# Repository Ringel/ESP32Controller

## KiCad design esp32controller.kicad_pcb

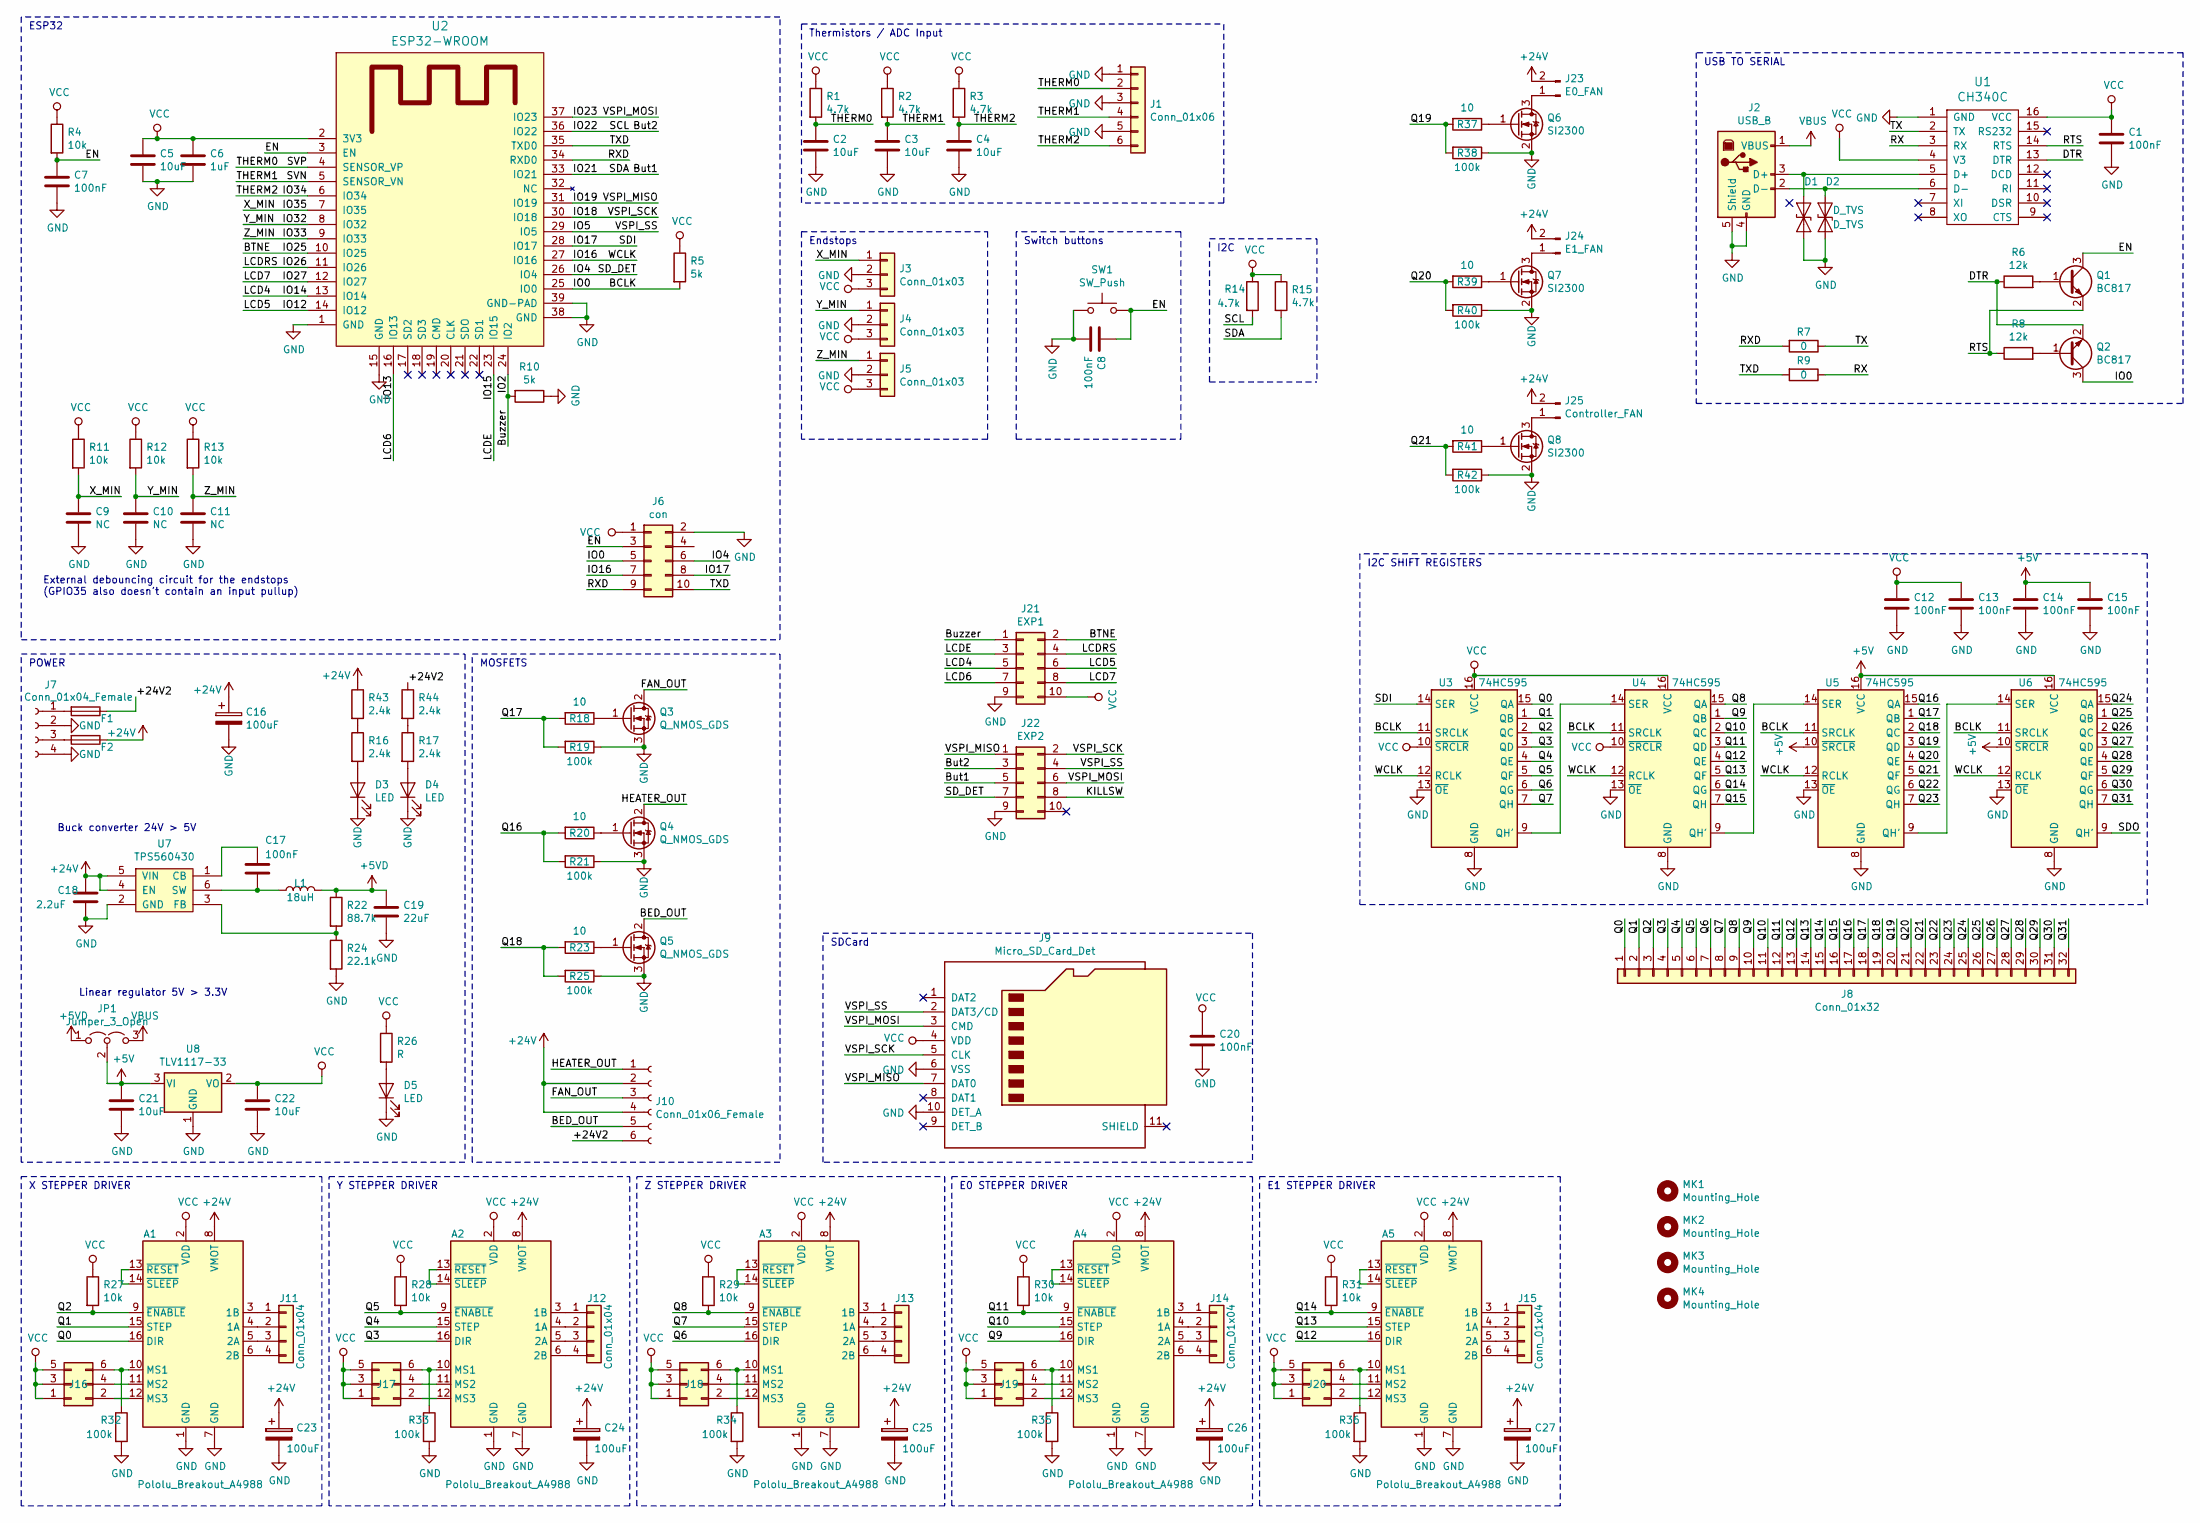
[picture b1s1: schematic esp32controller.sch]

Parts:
A1, A2, A3, A4, A5: Pololu_Breakout_A4988; Pololu_Breakout-16_15.2x20.3mm
C1, C7, C8, C12, C13, C14, C15, C17, C20: 100nF; C_0805_2012Metric
C2, C3, C4, C5, C21, C22: 10uF; C_0805_2012Metric
C6: 1uF; C_0805_2012Metric
C9, C10, C11: NC; C_0805_2012Metric
C16, C23, C24, C25, C26, C27: 100uF; CP_Elec_6.3x7.7
C18: 2.2uF; C_0805_2012Metric
C19: 22uF; C_0805_2012Metric
D1, D2: D_TVS; D_0603_1608Metric
D3, D4, D5: LED; LED_0805_2012Metric
F1, F2: Fuse; Fuse_0679H
J1: Conn_01x06; PinHeader_2x03_P2.54mm_Vertical
J2: USB_B; USB_B_OST_USB-B1HSxx_Horizontal
J3, J4, J5: Conn_01x03; PinHeader_1x03_P2.54mm_Vertical
J6: con; PinHeader_2x05_P2.54mm_Vertical
J7: Conn_01x04_Female; KP7.62x4
J8: Conn_01x32; PinHeader_2x16_P2.54mm_Vertical
J9: Micro_SD_Card_Det; microsd
J10: Conn_01x06_Female; KP7.62x6
J11, J12, J13, J14, J15: Conn_01x04; Socket_Strip_Straight_1x04_Pitch2.54mm_dual
J16, J17, J18, J19, J20: Conn_02x03_Odd_Even; PinHeader_2x03_P2.54mm_Vertical
J21: EXP1; PinHeader_2x05_P2.54mm_Vertical
J22: EXP2; PinHeader_2x05_P2.54mm_Vertical
J23: E0_FAN; PinHeader_1x02_P2.54mm_Vertical
J24: E1_FAN; PinHeader_1x02_P2.54mm_Vertical
J25: Controller_FAN; PinHeader_1x02_P2.54mm_Vertical
JP1: Jumper_3_Open; PinHeader_1x03_P2.54mm_Vertical
L1: 18uH; SDR0403
MK1, MK2, MK3, MK4: Mounting_Hole; MountingHole_3.2mm_M3
Q1, Q2: BC817; SOT-23
Q3, Q4, Q5: Q_NMOS_GDS; TO-252-2
Q6, Q7, Q8: SI2300; SOT-23
R1, R2, R3, R14, R15: 4.7k; R_0805_2012Metric
R4, R11, R12, R13, R27, R28, R29, R30, R31: 10k; R_0805_2012Metric
R5, R10: 5k; R_0805_2012Metric
R6, R8: 12k; R_0805_2012Metric
R7, R9: 0; R_0805_2012Metric
R16, R17, R43, R44: 2.4k; R_0805_2012Metric
R18, R20, R23, R37, R39, R41: 10; R_0805_2012Metric
R19, R21, R25, R32, R33, R34, R35, R36, R38, R40, R42: 100k; R_0805_2012Metric
R22: 88.7k; R_0805_2012Metric
R24: 22.1k; R_0805_2012Metric
R26: R; R_0805_2012Metric
SW1: SW_Push; SW_Push_1P1T_NO_6x6mm_H9.5mm
U1: CH340C; SOP-16_4.4x10.4mm_P1.27mm
U2: ESP32-WROOM
U3, U4, U5, U6: 74HC595; TSSOP-16_4.4x5mm_P0.65mm
U7: TPS560430; SOT-23-6
U8: TLV1117-33; SOT-223-3_TabPin2

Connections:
+5V: C14.1, C15.1, C21.1, JP1.2 (C), U5.10 (~SRCLR), U5.16 (VCC), U6.10 (~SRCLR), U6.16 (VCC), U8.3 (VI)
+5VD: C19.1, JP1.1 (A), L1.2, R22.1
+24V: A1.8 (VMOT), A2.8 (VMOT), A3.8 (VMOT), A4.8 (VMOT), A5.8 (VMOT), C16.1, C18.1, C23.1, C24.1, C25.1, C26.1, C27.1, F2.1, J10.2, J10.4, J23.2, J24.2, J25.2, R43.1, U7.4 (EN), U7.5 (VIN)
/+24V2: F1.1, J10.6, R44.1
/BCLK: J6.5, Q2.3 (C), R5.2, U2.25 (IO0), U3.11 (SRCLK), U4.11 (SRCLK), U5.11 (SRCLK), U6.11 (SRCLK)
/BED_OUT: J10.5, Q5.2 (D)
/BTNE: J21.2, U2.10 (IO25)
/But1: J22.5, R15.2, U2.33 (IO21)
/But2: J22.3, R14.2, U2.36 (IO22)
/Buzzer: J21.1, R10.2, U2.24 (IO2)
/DTR: Q2.2 (E), R6.1, U1.13 (DTR)
/EN: C7.1, C8.1, J6.3, Q1.3 (C), R4.2, SW1.2, U2.3 (EN)
/FAN_OUT: J10.3, Q3.2 (D)
/HEATER_OUT: J10.1, Q4.2 (D)
/IO4: J6.6, J22.7, U2.26 (IO4)
/IO5: J9.2 (DAT3/CD), J22.4, U2.29 (IO5)
/IO12: J21.6, U2.14 (IO12)
/IO13: J21.7, U2.16 (IO13)
/IO14: J21.5, U2.13 (IO14)
/IO15: J21.3, U2.23 (IO15)
/IO16: J6.7, U2.27 (IO16), U3.12 (RCLK), U4.12 (RCLK), U5.12 (RCLK), U6.12 (RCLK)
/IO17: J6.8, U2.28 (IO17), U3.14 (SER)
/IO18: J9.5 (CLK), J22.2, U2.30 (IO18)
/IO19: J9.7 (DAT0), J22.1, U2.31 (IO19)
/IO23: J9.3 (CMD), J22.6, U2.37 (IO23)
/IO26: J21.4, U2.11 (IO26)
/IO27: J21.8, U2.12 (IO27)
/IO32: C10.1, J4.1, R12.2, U2.8 (IO32)
/IO33: C11.1, J5.1, R13.2, U2.9 (IO33)
/IO34: C4.1, J1.6, R3.2, U2.6 (IO34)
/IO35: C9.1, J3.1, R11.2, U2.7 (IO35)
/Q0: A1.16 (DIR), J8.1, U3.15 (QA)
/Q1: A1.15 (STEP), J8.2, U3.1 (QB)
/Q2: A1.9 (~ENABLE), J8.3, R27.2, U3.2 (QC)
/Q3: A2.16 (DIR), J8.4, U3.3 (QD)
/Q4: A2.15 (STEP), J8.5, U3.4 (QE)
/Q5: A2.9 (~ENABLE), J8.6, R28.2, U3.5 (QF)
/Q6: A3.16 (DIR), J8.7, U3.6 (QG)
/Q7: A3.15 (STEP), J8.8, U3.7 (QH)
/Q8: A3.9 (~ENABLE), J8.9, R29.2, U4.15 (QA)
/Q9: A4.16 (DIR), J8.10, U4.1 (QB)
/Q10: A4.15 (STEP), J8.11, U4.2 (QC)
/Q11: A4.9 (~ENABLE), J8.12, R30.2, U4.3 (QD)
/Q12: A5.16 (DIR), J8.13, U4.4 (QE)
/Q13: A5.15 (STEP), J8.14, U4.5 (QF)
/Q14: A5.9 (~ENABLE), J8.15, R31.2, U4.6 (QG)
/Q15: J8.16, U4.7 (QH)
/Q16: J8.17, R20.2, R21.2, U5.15 (QA)
/Q17: J8.18, R18.2, R19.2, U5.1 (QB)
/Q18: J8.19, R23.2, R25.2, U5.2 (QC)
/Q19: J8.20, R37.2, R38.2, U5.3 (QD)
/Q20: J8.21, R39.2, R40.2, U5.4 (QE)
/Q21: J8.22, R41.2, R42.2, U5.5 (QF)
/Q22: J8.23, U5.6 (QG)
/Q23: J8.24, U5.7 (QH)
/Q24: J8.25, U6.15 (QA)
/Q25: J8.26, U6.1 (QB)
/Q26: J8.27, U6.2 (QC)
/Q27: J8.28, U6.3 (QD)
/Q28: J8.29, U6.4 (QE)
/Q29: J8.30, U6.5 (QF)
/Q30: J8.31, U6.6 (QG)
/Q31: J8.32, U6.7 (QH)
/RTS: Q1.2 (E), R8.1, U1.14 (RTS)
/RX: R9.1, U1.3 (RX)
/RXD: J6.9, R7.2, U2.34 (RXD0)
/SVN: C3.1, J1.4, R2.2, U2.5 (SENSOR_VN)
/SVP: C2.1, J1.2, R1.2, U2.4 (SENSOR_VP)
/TX: R7.1, U1.2 (TX)
/TXD: J6.10, R9.2, U2.35 (TXD0)
GND: A1.1 (GND), A1.7 (GND), A2.1 (GND), A2.7 (GND), A3.1 (GND), A3.7 (GND), A4.1 (GND), A4.7 (GND), A5.1 (GND), A5.7 (GND), C1.2, C2.2, C3.2, C4.2, C5.2, C6.2, C7.2, C8.2, C9.2, C10.2, C11.2, C12.2, C13.2, C14.2, C15.2, C16.2, C18.2, C19.2, C20.2, C21.2, C22.2, C23.2, C24.2, C25.2, C26.2, C27.2, D1.2 (A2), D2.2 (A2), D3.1 (K), D4.1 (K), D5.1 (K), J1.1, J1.3, J1.5, J2.4 (GND), J2.5 (Shield), J3.2, J4.2, J5.2, J6.2, J7.2, J7.4, J9.6 (VSS), J9.10 (DET_A), J21.9, J22.9, Q3.3 (S), Q4.3 (S), Q5.3 (S), Q6.2 (S), Q7.2 (S), Q8.2 (S), R10.1, R19.1, R21.1, R24.2, R25.1, R32.2, R33.2, R34.2, R35.2, R36.2, R38.1, R40.1, R42.1, SW1.1, U1.1 (GND), U2.1 (GND), U2.15 (GND), U2.38 (GND), U2.39 (GND-PAD), U3.8 (GND), U3.13 (~OE), U4.8 (GND), U4.13 (~OE), U5.8 (GND), U5.13 (~OE), U6.8 (GND), U6.13 (~OE), U7.2 (GND), U8.1 (GND)
unnamed: A1.3 (1B), J11.1
unnamed: A1.4 (1A), J11.2
unnamed: A1.5 (2A), J11.3
unnamed: A1.6 (2B), J11.4
unnamed: A1.10 (MS1), J16.6, R32.1
unnamed: A1.11 (MS2), J16.4
unnamed: A1.12 (MS3), J16.2
unnamed: A1.13 (~RESET), A1.14 (~SLEEP)
unnamed: A2.3 (1B), J12.1
unnamed: A2.4 (1A), J12.2
unnamed: A2.5 (2A), J12.3
unnamed: A2.6 (2B), J12.4
unnamed: A2.10 (MS1), J17.6, R33.1
unnamed: A2.11 (MS2), J17.4
unnamed: A2.12 (MS3), J17.2
unnamed: A2.13 (~RESET), A2.14 (~SLEEP)
unnamed: A3.3 (1B), J13.1
unnamed: A3.4 (1A), J13.2
unnamed: A3.5 (2A), J13.3
unnamed: A3.6 (2B), J13.4
unnamed: A3.10 (MS1), J18.6, R34.1
unnamed: A3.11 (MS2), J18.4
unnamed: A3.12 (MS3), J18.2
unnamed: A3.13 (~RESET), A3.14 (~SLEEP)
unnamed: A4.3 (1B), J14.1
unnamed: A4.4 (1A), J14.2
unnamed: A4.5 (2A), J14.3
unnamed: A4.6 (2B), J14.4
unnamed: A4.10 (MS1), J19.6, R35.1
unnamed: A4.11 (MS2), J19.4
unnamed: A4.12 (MS3), J19.2
unnamed: A4.13 (~RESET), A4.14 (~SLEEP)
unnamed: A5.3 (1B), J15.1
unnamed: A5.4 (1A), J15.2
unnamed: A5.5 (2A), J15.3
unnamed: A5.6 (2B), J15.4
unnamed: A5.10 (MS1), J20.6, R36.1
unnamed: A5.11 (MS2), J20.4
unnamed: A5.12 (MS3), J20.2
unnamed: A5.13 (~RESET), A5.14 (~SLEEP)
unnamed: C17.1, U7.1 (CB)
unnamed: C17.2, L1.1, U7.6 (SW)
unnamed: D1.1 (A1), J2.3 (D+), U1.5 (D+)
unnamed: D2.1 (A1), J2.2 (D-), U1.6 (D-)
unnamed: D3.2 (A), R16.2
unnamed: D4.2 (A), R17.2
unnamed: D5.2 (A), R26.2
unnamed: F1.2, J7.1
unnamed: F2.2, J7.3
unnamed: J23.1, Q6.3 (D)
unnamed: J24.1, Q7.3 (D)
unnamed: J25.1, Q8.3 (D)
unnamed: Q1.1 (B), R6.2
unnamed: Q2.1 (B), R8.2
unnamed: Q3.1 (G), R18.1
unnamed: Q4.1 (G), R20.1
unnamed: Q5.1 (G), R23.1
unnamed: Q6.1 (G), R37.1
unnamed: Q7.1 (G), R39.1
unnamed: Q8.1 (G), R41.1
unnamed: R16.1, R43.2
unnamed: R17.1, R44.2
unnamed: R22.2, R24.1, U7.3 (FB)
unnamed: U3.9 (QH'), U4.14 (SER)
unnamed: U4.9 (QH'), U5.14 (SER)
unnamed: U5.9 (QH'), U6.14 (SER)
VBUS: J2.1 (VBUS), JP1.3 (B)
VCC: A1.2 (VDD), A2.2 (VDD), A3.2 (VDD), A4.2 (VDD), A5.2 (VDD), C1.1, C5.1, C6.1, C12.1, C13.1, C20.1, C22.1, J3.3, J4.3, J5.3, J6.1, J9.4 (VDD), J16.1, J16.3, J16.5, J17.1, J17.3, J17.5, J18.1, J18.3, J18.5, J19.1, J19.3, J19.5, J20.1, J20.3, J20.5, J21.10, R1.1, R2.1, R3.1, R4.1, R5.1, R11.1, R12.1, R13.1, R14.1, R15.1, R26.1, R27.1, R28.1, R29.1, R30.1, R31.1, U1.4 (V3), U1.16 (VCC), U2.2 (3V3), U3.10 (~SRCLR), U3.16 (VCC), U4.10 (~SRCLR), U4.16 (VCC), U8.2 (VO)

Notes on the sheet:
X STEPPER DRIVER
Y STEPPER DRIVER
Z STEPPER DRIVER
E0 STEPPER DRIVER
I2C
Thermistors / ADC Input
Endstops
USB TO SERIAL
SDCard
Buck converter 24V > 5V
Linear regulator 5V > 3.3V
POWER
MOSFETS
ESP32
E1 STEPPER DRIVER
External debouncing circuit for the endstops (GPIO35 also doesn't contain an input pullup)
I2C SHIFT REGISTERS
Switch buttons

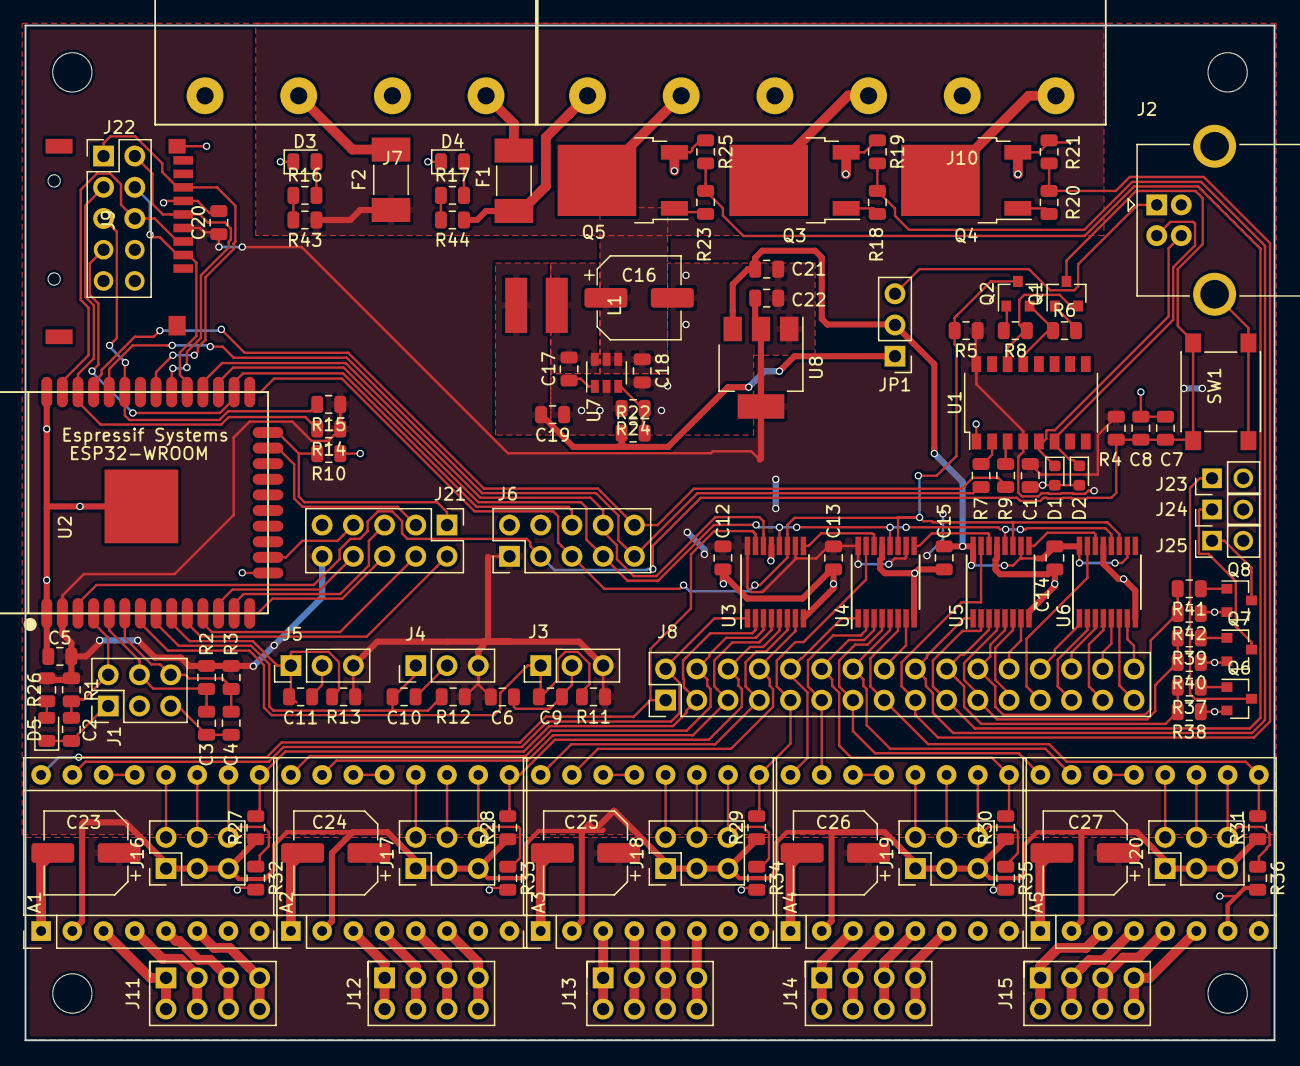
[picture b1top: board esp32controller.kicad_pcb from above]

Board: 2 copper layers, 101.6 x 82.6 mm, 131 parts (0 on the bottom side), 139 nets.

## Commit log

2019-06-16 Shuffled pins, added Display Connector and more FETs, Supplied Shiftregister with 5V for higher Gate Drive voltage
2019-06-16 Routed R3 Board
